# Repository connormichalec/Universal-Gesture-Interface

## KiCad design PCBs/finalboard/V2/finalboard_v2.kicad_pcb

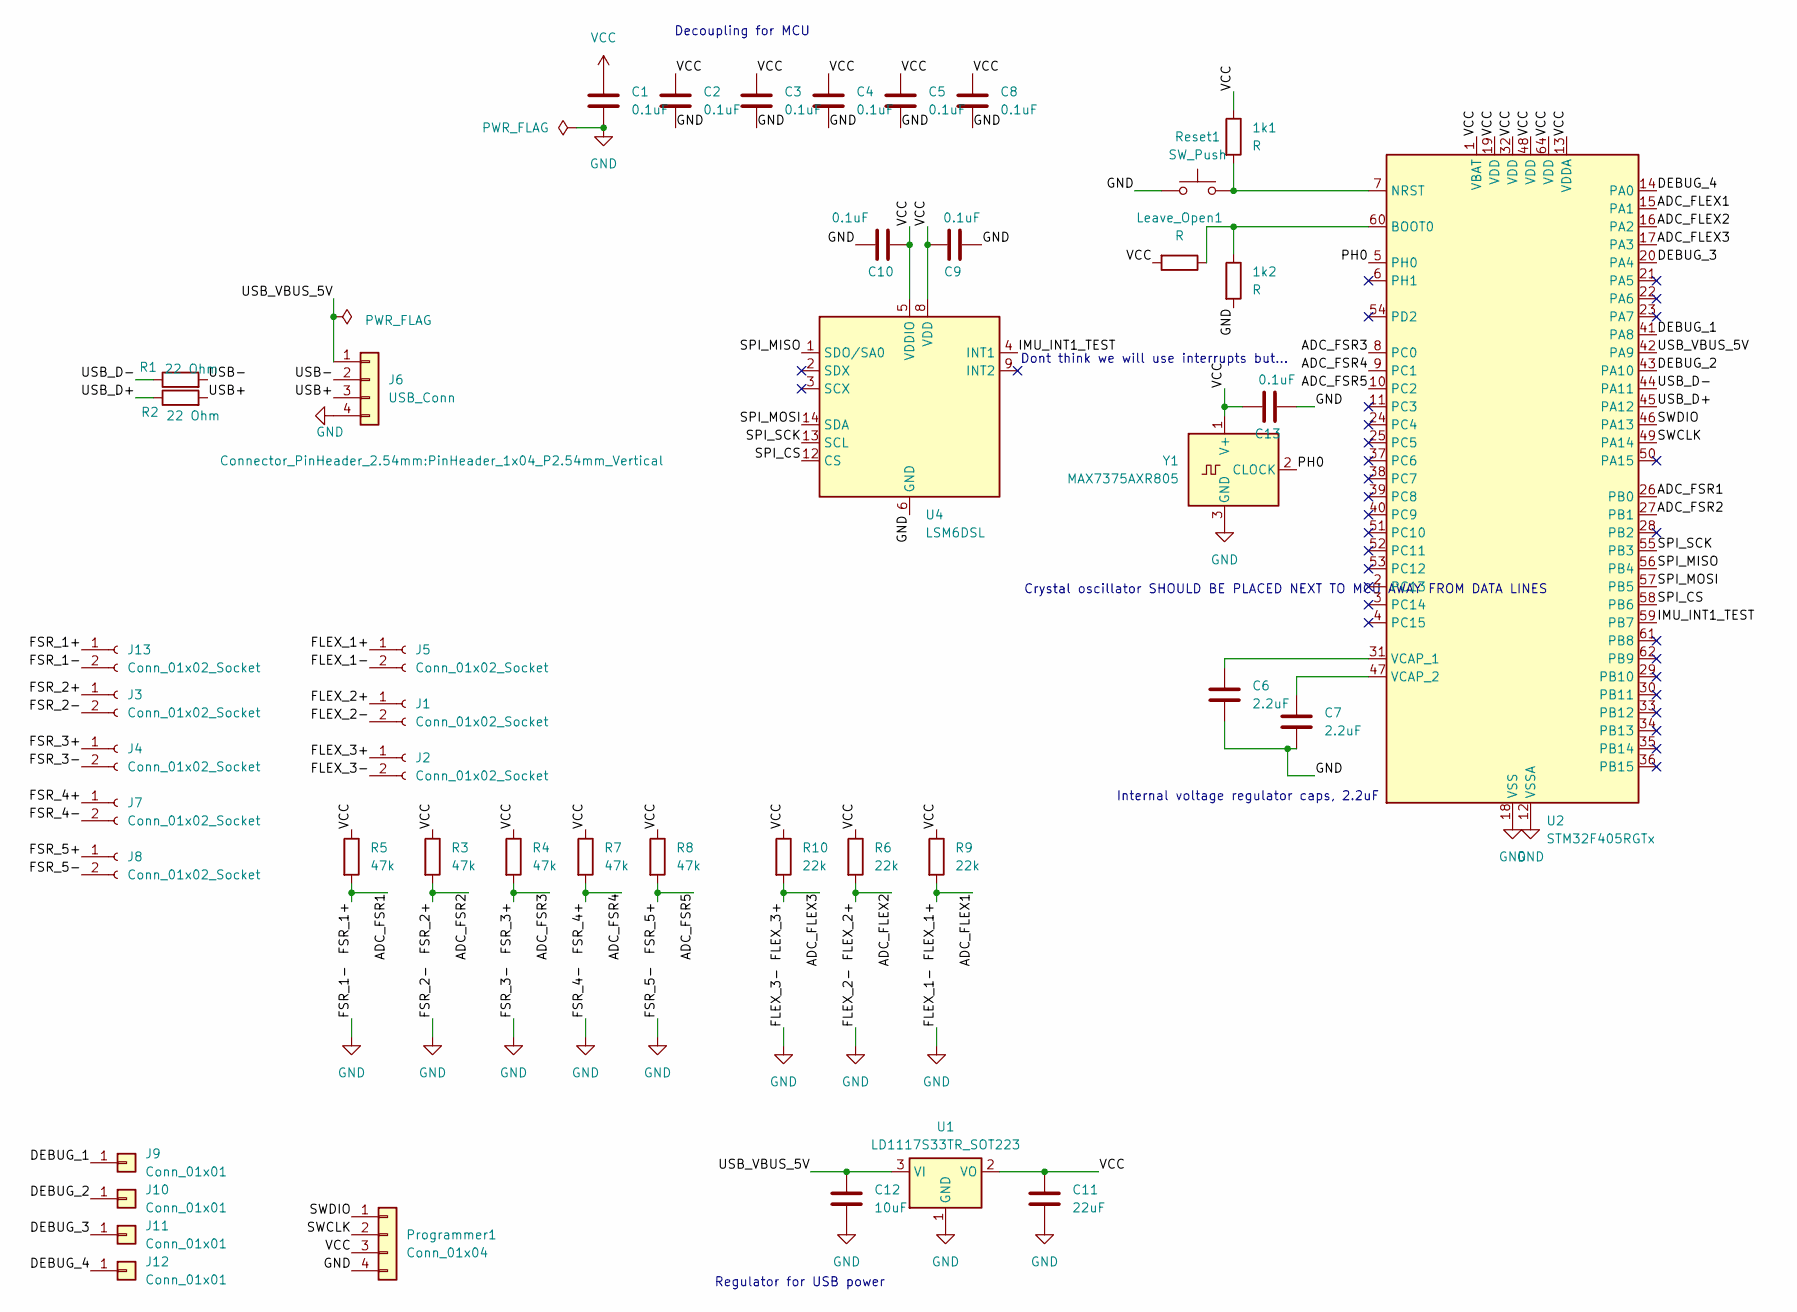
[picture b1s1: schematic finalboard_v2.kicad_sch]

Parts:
1k1, 1k2: R; R_0603_1608Metric_Pad0.98x0.95mm_HandSolder
C1, C2, C3, C4, C5, C8, C9, C10, C13: 0.1uF; C_0603_1608Metric_Pad1.08x0.95mm_HandSolder
C6, C7: 2.2uF; C_0603_1608Metric_Pad1.08x0.95mm_HandSolder
C11: 22uF; C_0603_1608Metric_Pad1.08x0.95mm_HandSolder
C12: 10uF; C_0603_1608Metric_Pad1.08x0.95mm_HandSolder
J1, J2, J3, J4, J5, J7, J8, J13: Conn_01x02_Socket; PinHeader_1x02_P2.54mm_Vertical
J6: USB_Conn; PinHeader_1x04_P2.54mm_Vertical
J9, J10, J11, J12: Conn_01x01; TestPoint_Pad_1.5x1.5mm
Leave_Open1: R; R_Axial_DIN0204_L3.6mm_D1.6mm_P7.62mm_Horizontal
Programmer1: Conn_01x04; PinHeader_1x04_P2.54mm_Vertical
R1, R2: 22 Ohm; R_0603_1608Metric_Pad0.98x0.95mm_HandSolder
R3, R4, R5, R7, R8: 47k; R_0603_1608Metric_Pad0.98x0.95mm_HandSolder
R6, R9, R10: 22k; R_0603_1608Metric_Pad0.98x0.95mm_HandSolder
Reset1: SW_Push; SW_PUSH_6mm_H4.3mm
U1: LD1117S33TR_SOT223; SOT-223-3_TabPin2
U2: STM32F405RGTx; LQFP-64_10x10mm_P0.5mm
U4: LSM6DSL; LGA-14_3x2.5mm_P0.5mm_LayoutBorder3x4y
Y1: MAX7375AXR805; SOT-323_SC-70

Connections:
/ADC_FLEX1: J5.1, R9.2, U2.15 (PA1)
/ADC_FLEX2: J1.1, R6.2, U2.16 (PA2)
/ADC_FLEX3: J2.1, R10.2, U2.17 (PA3)
/ADC_FSR1: J13.1, R5.2, U2.26 (PB0)
/ADC_FSR2: J3.1, R3.2, U2.27 (PB1)
/ADC_FSR3: J4.1, R4.2, U2.8 (PC0)
/ADC_FSR4: J7.1, R7.2, U2.9 (PC1)
/ADC_FSR5: J8.1, R8.2, U2.10 (PC2)
/DEBUG_1: J9.1, U2.41 (PA8)
/DEBUG_2: J10.1, U2.43 (PA10)
/DEBUG_3: J11.1, U2.20 (PA4)
/DEBUG_4: J12.1, U2.14 (PA0)
/IMU_INT1_TEST: U2.59 (PB7), U4.4 (INT1)
/PH0: U2.5 (PH0), Y1.2 (CLOCK)
/SPI_CS: U2.58 (PB6), U4.12 (CS)
/SPI_MISO: U2.56 (PB4), U4.1 (SDO/SA0)
/SPI_MOSI: U2.57 (PB5), U4.14 (SDA)
/SPI_SCK: U2.55 (PB3), U4.13 (SCL)
/SWCLK: Programmer1.2, U2.49 (PA14)
/SWDIO: Programmer1.1, U2.46 (PA13)
/USB+: J6.3, R2.2
/USB-: J6.2, R1.2
/USB_D+: R2.1, U2.45 (PA12)
/USB_D-: R1.1, U2.44 (PA11)
/USB_VBUS_5V: C12.1, J6.1, U1.3 (VI), U2.42 (PA9)
GND: 1k2.2, C1.2, C2.2, C3.2, C4.2, C5.2, C6.2, C7.2, C8.2, C9.2, C10.1, C11.2, C12.2, C13.2, J1.2, J2.2, J3.2, J4.2, J5.2, J6.4, J7.2, J8.2, J13.2, Programmer1.4, Reset1.1, U1.1 (GND), U2.12 (VSSA), U2.18 (VSS), U2.63 (VSS), U4.6 (GND), U4.7 (GND), Y1.3 (GND)
unnamed: 1k2.1, Leave_Open1.1, U2.60 (BOOT0)
unnamed: 1k1.2, Reset1.2, U2.7 (NRST)
unnamed: C6.1, U2.31 (VCAP_1)
unnamed: C7.1, U2.47 (VCAP_2)
VCC: 1k1.1, C1.1, C2.1, C3.1, C4.1, C5.1, C8.1, C9.1, C10.2, C11.1, C13.1, Leave_Open1.2, Programmer1.3, R3.1, R4.1, R5.1, R6.1, R7.1, R8.1, R9.1, R10.1, U1.2 (VO), U2.1 (VBAT), U2.13 (VDDA), U2.19 (VDD), U2.32 (VDD), U2.48 (VDD), U2.64 (VDD), U4.5 (VDDIO), U4.8 (VDD), Y1.1 (V+)

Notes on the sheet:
Regulator for USB power
Internal voltage regulator caps, 2.2uF
Decoupling for MCU
Crystal oscillator SHOULD BE PLACED NEXT TO MCU AWAY FROM DATA LINES
Dont think we will use interrupts but...

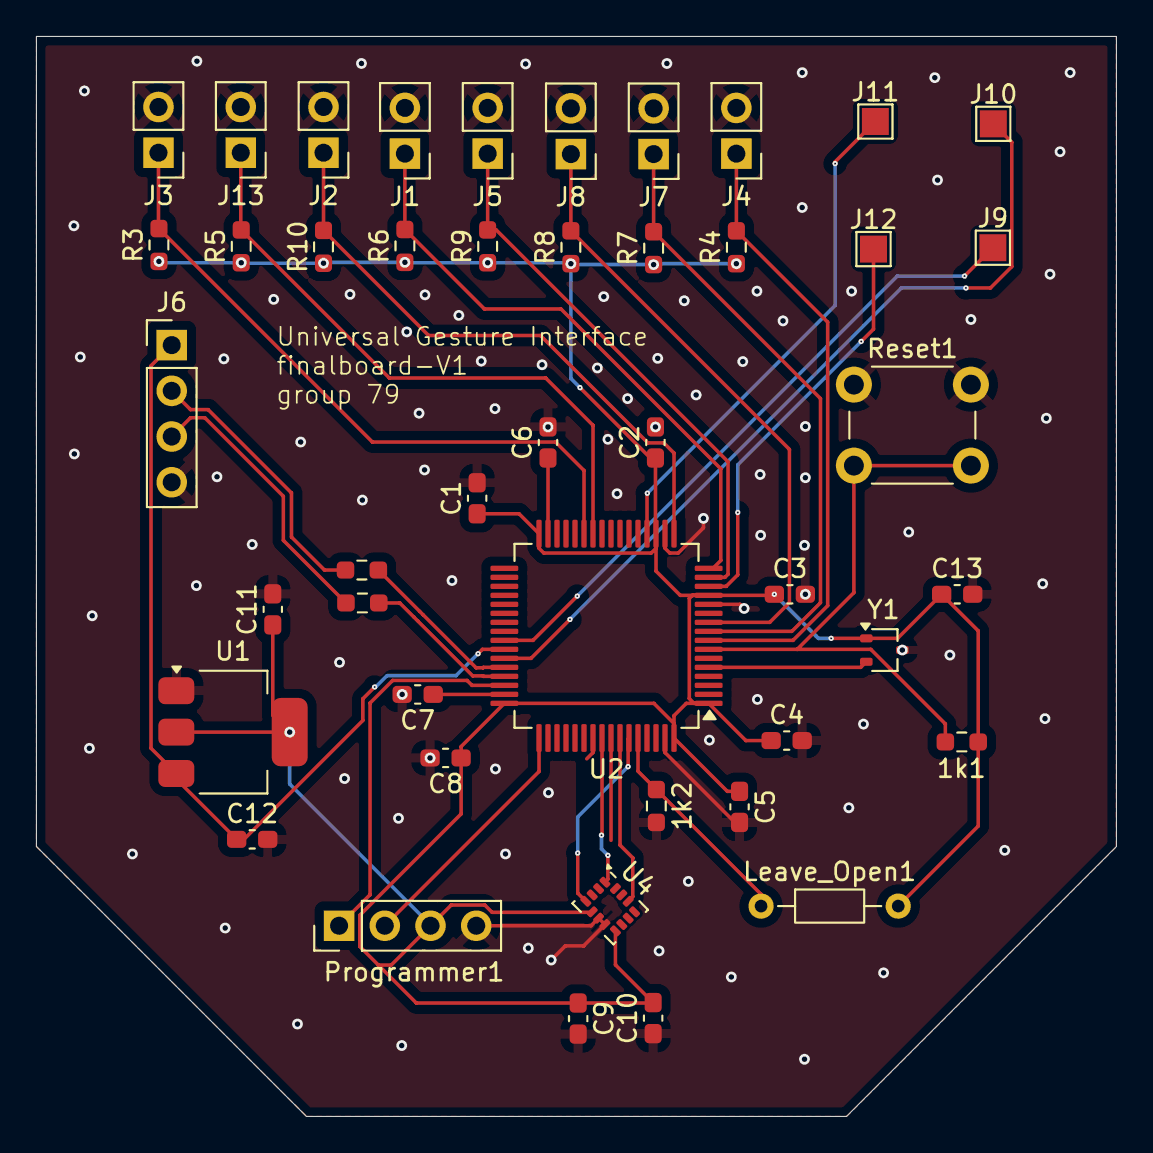
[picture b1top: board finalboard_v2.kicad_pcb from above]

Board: 2 copper layers, 60.0 x 60.0 mm, 45 parts (0 on the bottom side), 31 nets.

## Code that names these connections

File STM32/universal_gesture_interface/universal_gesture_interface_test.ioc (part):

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Mcu.Name=STM32F405RGTx
Mcu.Package=LQFP64
Mcu.UserName=STM32F405RGTx
PA0-WKUP.Signal=GPIO_Output
PA1.GPIOParameters=GPIO_Label
PA1.GPIO_Label=Fsr_index
PA1.Signal=ADCx_IN1
PA11.Mode=Device_Only
PA11.Signal=USB_OTG_FS_DM
PA12.Mode=Device_Only
PA12.Signal=USB_OTG_FS_DP
PA13.Signal=SYS_JTMS-SWDIO
PA14.Signal=SYS_JTCK-SWCLK
PA2.GPIOParameters=GPIO_Label
PA2.GPIO_Label=Fsr_thumb
PA2.Signal=ADCx_IN2
PA3.GPIOParameters=GPIO_Label
PA3.GPIO_Label=Flex_middle
PA3.Signal=ADCx_IN3
PA8.Mode=Clock-out-1
PA8.Signal=RCC_MCO_1
PA9.Signal=USB_OTG_FS_VBUS
PB0.GPIOParameters=GPIO_Label
PB0.GPIO_Label=Flex_index
PB0.Signal=ADCx_IN8
PB3.Mode=Full_Duplex_Master
PB3.Signal=SPI1_SCK
PB4.Mode=Full_Duplex_Master
PB4.Signal=SPI1_MISO
PB5.Mode=Full_Duplex_Master
PB5.Signal=SPI1_MOSI
PB6.GPIOParameters=GPIO_PuPd,GPIO_Label
PB6.GPIO_Label=SPI1_CS
PB6.GPIO_PuPd=GPIO_NOPULL
PB6.Signal=GPIO_Output
PB7.GPIOParameters=GPIO_Label
PB7.GPIO_Label=IMU_INT1
PB7.Signal=GPIO_Output
PC0.Signal=ADCx_IN10
PC2.GPIOParameters=GPIO_Label
PC2.GPIO_Label=Fsr_middle
PC2.Signal=ADCx_IN12
PH0-OSC_IN.Mode=HSE-External-Oscillator
PH0-OSC_IN.Signal=RCC_OSC_IN
PH1-OSC_OUT.Mode=HSE-External-Oscillator
PH1-OSC_OUT.Signal=RCC_OSC_OUT
RCC.HSE_VALUE=8000000
RCC.SYSCLKFreq_VALUE=168000000
RCC.SYSCLKSource=RCC_SYSCLKSOURCE_PLLCLK
board=custom

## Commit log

2026-02-19 Testboard schematic finished, needs layout
2026-02-20 V1 layout done (its kinda crappy tho)
2026-02-20 V2 pcb schematic done - switched IMU. needs layout from kenobi
2026-02-24 V2 updated for USB
2026-02-25 V2 schematic done - awaiting layout from kenobi
2026-03-02 notebook added for connor
2026-03-02 testing formatting
    Added initial README for Connor's notebook with project objectives and dates.
2026-03-02 test format 2
2026-03-02 Update notebook
2026-03-12 Finalboard schematic done, awaiting layout from kenboi
2026-03-13 Finalboard-V1 layout done (by kenobi)
2026-03-26 upload stm32 project
2026-03-26 Basic USB functionality works, mouse test works
2026-03-28 Basic ADC working
2026-03-28 ping test for imu works (frankenstein pcb)
2026-03-28 Edit finalboard v2 to fix pinout on imu
2026-03-29 Update README with final board development details
    Added a new section for the final board development and updated the existing content for clarity and organization.
2026-03-29 Document test board assembly and initial configuration
    Added new entries for test board assembly and configuration, detailing the soldering process and initial tests.
2026-03-29 Update README with new test USB connectivity section
    Added new entries for test USB connectivity and updated previous entries for clarity.
2026-03-29 IMU tests working! (on frankenstein)
2026-03-30 Revise README with project updates and milestones
    Updated README to include new project developments and milestones from February to March 2026, detailing the progress on the Universal Gesture Interface project, including PCB schematics, assembly, U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
2026-04-01 Adding filtering, currently can't test due to broken(?) hardware
2026-04-05 Basic mouse movement, added extra tests
2026-04-06 Polished up mouse movement, flex sensor is low passed and now triggers scrolling
2026-04-26 Basic gesture detection framework, all sensor data good
2026-04-26 KEYBOARD control works
2026-04-28 Working on velocity integration, new message protocol
2026-04-28 HID fake serial
2026-04-28 Backing up before merge
2026-04-28 Refactoring keyboard and mouse stuff
2026-05-08 Revise Connor's notebook with project updates
    Updated README.md to reflect project progress and changes.
